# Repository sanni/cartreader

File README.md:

<br>    
<br>    
<br>   
<br>
We have moved, please visit us at https://github.com/oscartreader 🚀
<br>    
<br>    
<br>   
<br>
<br>    
<br>    
<br>   

# Open Source Cartridge Reader
This project represents a community-driven effort to provide an easy to build and easy to modify cartridge dumper.
Its main purpose is to dump a video game's ROM and save file to an SD card without the need of a PC.

For any questions you can use the [Discussions](https://github.com/sanni/cartreader/discussions) and/or [Issues](https://github.com/sanni/cartreader/issues) section here on GitHub, visit the accompanying thread in the [Arduino Forum](http://forum.arduino.cc/index.php?topic=158974.9001) or check out our [community discord server](https://discord.gg/YVxv7BnzXt), where you can reach most of the devs directly.

Also be sure to check the guides in the [Wiki](https://github.com/sanni/cartreader/wiki) too.

Happy making. 🔧🔨😊

#### Features:
- Modular design
- Stand-alone operation
- Easy to modify open-source code
- Portable when used together with a power bank

#### Supported Systems:
- NES/Famicom/Family Basic
- Super Nintendo/Super Famicom (including SF Memory, Satellaview, Sufami Turbo, and Game Processor RAM Cassettes)
- Nintendo 64 (including Controller Pak, Gameshark, and Xplorer 64)
- Game Boy Color (including GB Memory, Codebreaker, and Gameshark)
- Game Boy Advance
- Sega Mega Drive/Genesis
- Sega Master System

#### Supported with adapters:
- Virtual Boy
- Pokémon Mini
- Sega Game Gear
- Sega Mark III
- Sega SG-1000/SC-3000
- Sega Cards
- PC Engine/TurboGrafx-16/SuperGrafx
- WonderSwan (Color)
- NeoGeo Pocket (Color)
- Intellivision
- ColecoVision
- Benesse Pocket Challenge W
- Benesse Pocket Challenge V2
- Watara Supervision
- Atari 8-bit Computer (400/800/XL/XE)
- Atari 2600/5200/7800
- Atari Lynx
- Atari Jaguar
- Emerson Arcadia 2001
- Fairchild Channel F
- Magnavox Odyssey 2/Philips Videopac+
- Super A'Can
- MSX
- Casio PV-1000
- Casio Loopy
- Commodore VIC-20
- Commodore 64
- Vectrex
- Bally Astrocade
- Bandai Little Jammer
- Bandai Little Jammer Pro
- LeapFrog Leapster (L-MAX/Leapster2)
- RCA Studio II
- Texas Instruments TI-99
- Tomy Pyuuta
- TRS-80 Color Computer
- Vtech V.Smile (Baby/V.Motion)
- CPS3

#### Open Source Licenses:
- Software(everything in Cart_Reader folder) = GPL v3
- Hardware(everything in hardware folder) = CC BY 4.0
- Documentation(everything in the Wiki) = CC0 1.0

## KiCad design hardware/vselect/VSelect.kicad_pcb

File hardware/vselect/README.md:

# VSELECT: Automatic Voltage Selection Module

The VSELECT module automates voltage selection on HW5 by allowing the firmware to set the voltage. The module version is intended to be soldered in place of the voltage selection switch. You cannot use the VSELECT module and a power LED at the same time.

## Ordering the PCB and Installing the components

The VSELECT module requires SMD/SMC (surface-mounted devices/components) soldering. The pads have been extended slightly to aid in hand-soldering. While files suitable for use with JLCPCB's PCBA service have been included, these are unsuitable for most people to use due to the minimum order quantity. If you want fewer than 10 modules it will be cheaper to order them from someone selling pre-built ones.

## Installation

Instructions to build as well as to install the module have moved [to the wiki](https://github.com/sanni/cartreader/wiki/Automatic-Voltage-Selection).

## Configuration

The module requires code to function properly. The OSCR should still power on even without the code changes but the voltage will not automatically toggle. To enable automatic toggling, locate this bit of code:

```
/*==== HARDWARE MODULES ===========================================*/

/* [ Automatic Voltage Selection ---------------------------------- ]
    Enable this if you have the VSELECT module.
*/

//#define ENABLE_VSELECT
```

...and change it to:

```
/*==== HARDWARE MODULES ===========================================*/

/* [ Automatic Voltage Selection ---------------------------------- ]
    Enable this if you have the VSELECT module.
*/

#define ENABLE_VSELECT
```

After that simply update/program/flash your Arduino/OSCR as normal. Make sure you enable this every time you update. You can test that voltage switching is occurring with a multimeter by checking between ground and VCC.

## Updating
When the OSCR is using VSELECT-enabled firmware there are a few extra steps you need to take when flashing firmware. First, before connecting the OSCR to a computer, remove the SD card. Next, connect the OSCR to your computer and wait. Once it prompts you, press the button to set the voltage to 5V. Although you can flash the ATmega2560 while running at 3.3V it does not always work and seems more likely to cause the firmware to randomly be corrupt (sometimes right away, sometimes not for a few days). Although you can just reflash the firmware to it to resolve it, having to deal with it is rather inconvenient.

## Troubleshooting
If the 3.3V rail is not powered (i.e. you forgot to solder the jumper on the LCD) then when the module tries to switch to that it will power off the VCC rail. This will appear as a reboot loop where you'll see it briefly power on and then immediately power off only to immediately power on again. This is because the module starts in 5V mode and switches to 3.3V after the system boots and tells it to do so.

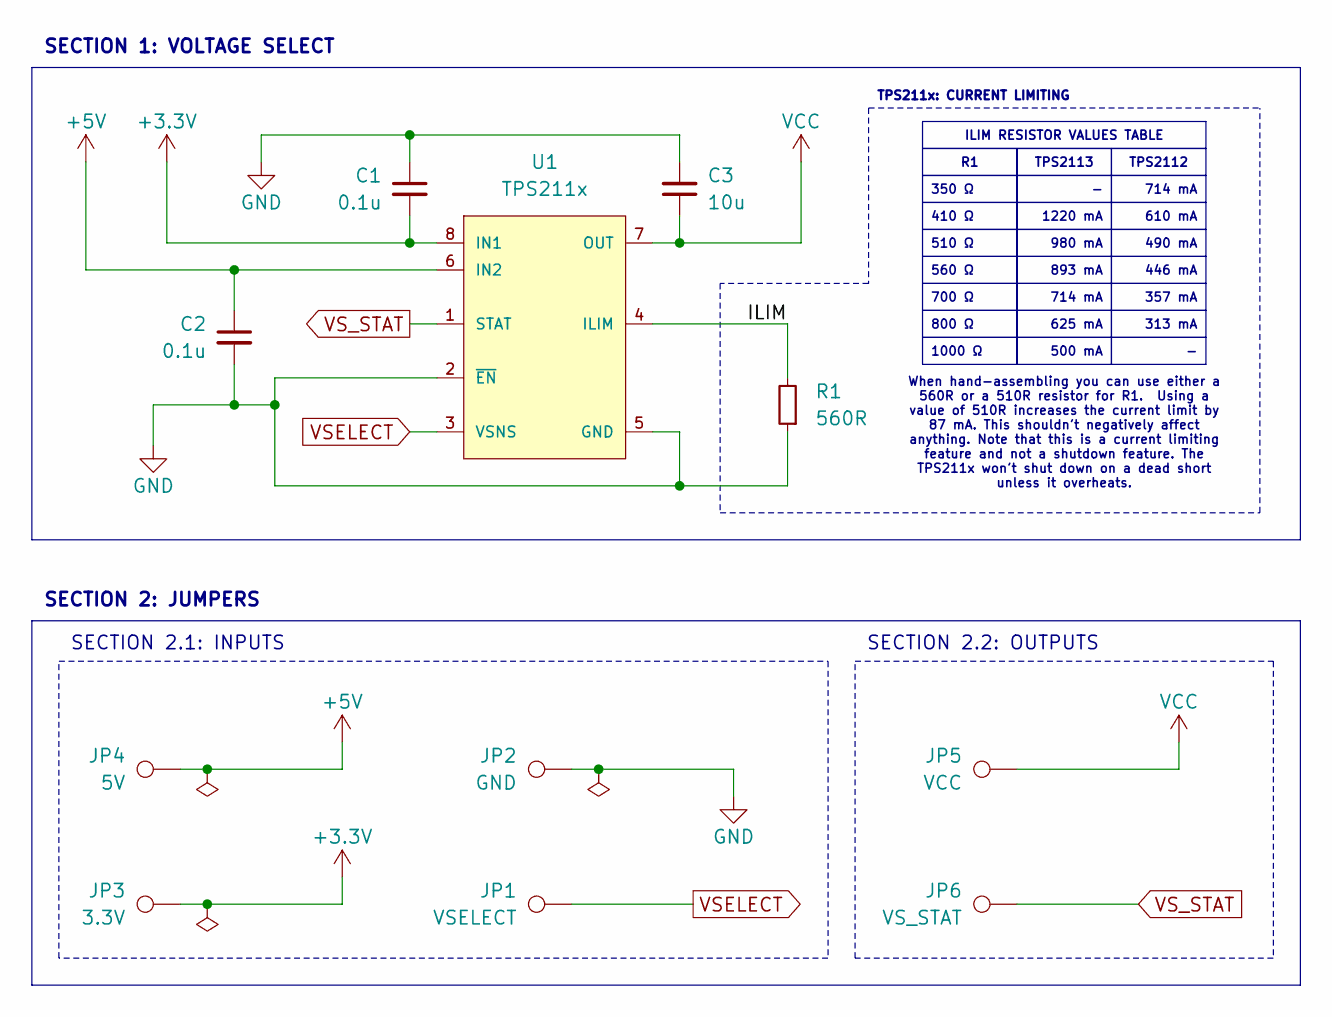
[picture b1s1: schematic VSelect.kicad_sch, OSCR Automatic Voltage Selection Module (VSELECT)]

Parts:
C1, C2: 0.1u; C_0402_1005Metric_Pad0.74x0.62mm_HandSolder; Part CL05B104KO5NNNC; LCSC C1525
C3: 10u; C_0402_1005Metric_Pad0.74x0.62mm_HandSolder; Part CL05A106MQ5NUNC; LCSC C15525
JP1: VSELECT; TestPoint_Pad_2.0x2.0mm
JP2: GND; TestPoint_Pad_2.0x2.0mm
JP3: 3.3V; Header - VSELECT - Switch Pad
JP4: 5V; Header - VSELECT - Switch Pad
JP5: VCC; Header - VSELECT - Switch Pad
JP6: VS_STAT; TestPoint_Pad_2.0x2.0mm
R1: 560R; R_0402_1005Metric_Pad0.72x0.64mm_HandSolder; Part 0402WGF5100TCE; LCSC C25123
U1: TPS211x; IC - VSELECT - TPS2113; Part Hand/TPS2113APWR (C130052); Machine/TPS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; LCSC C354512

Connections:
+3.3V: C1.2, JP3.1, U1.8 (IN1)
+5V: C2.1, JP4.1, U1.6 (IN2)
/ILIM: R1.2, U1.4 (ILIM)
GND: C1.1, C2.2, C3.2, JP2.1, R1.1, U1.2 (~EN), U1.5 (GND), U1.9 (GND)
VCC: C3.1, JP5.1, U1.7 (OUT)
VSELECT: JP1.1, U1.3 (VSNS)
VS_STAT: JP6.1, U1.1 (STAT)

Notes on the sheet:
350 Ω
SECTION 2: JUMPERS
700 Ω
TPS2113
510 Ω
446 mA
490 mA
980 mA
893 mA
1000 Ω
714 mA
313 mA
TPS211x: CURRENT LIMITING
500 mA
625 mA
560 Ω
357 mA
SECTION 2.2: OUTPUTS
610 mA
1220 mA
410 Ω
SECTION 2.1: INPUTS
ILIM RESISTOR VALUES TABLE
TPS2112
800 Ω
SECTION 1: VOLTAGE SELECT
When hand-assembling you can use either a 560R or a 510R resistor for R1. Using a value of 510R increases the current limit by 87 mA. This shouldn't negatively affect anything. Note that this is a current limiting feature and not a shutdown feature. The TPS211x won't shut down on a dead short unles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

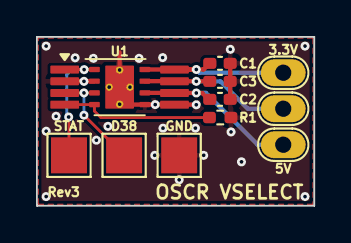
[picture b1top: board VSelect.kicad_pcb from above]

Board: 2 copper layers, 15.4 x 9.4 mm, 11 parts (0 on the bottom side), 7 nets.

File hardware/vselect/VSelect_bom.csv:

Designator,Footprint,Quantity,Value,LCSC Part #
"C1, C2",0402,2,0.1u,C1525
C3,0402,1,10u,C15525
R1,0402,1,560R,C25123
U1,IC - VSELECT - TPS2113,1,TPS211x,C354512

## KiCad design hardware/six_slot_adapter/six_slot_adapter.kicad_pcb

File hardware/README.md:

## All the files in this directory are licensed under the Attribution 4.0 International (CC BY 4.0)     

### This means that you are free to:    
- Share - copy and redistribute the material in any medium or format    
- Adapt - remix, transform, and build upon the material for any purpose, even commercially.  

The licensor cannot revoke these freedoms as long as you follow the license terms.    

### Under the following terms:    
- Attribution - You must give appropriate credit, provide a link to the license, and indicate if changes were made. You may do so in any reasonable manner, but not in any way that suggests the licensor endorses you or your use.    
- No additional restrictions - You may not apply legal terms or technological measures that legally restrict others from doing anything the license permits.    

More details: https://creativecommons.org/licenses/by/4.0/

##

You can view the schematic and PCB files using [KiCad](https://www.kicad.org/).   
To design your own adapters you can follow this [tutorial](https://github.com/sanni/cartreader/wiki/Designing-your-own-Adapters)   
Also check out the user contributions for even more adapters: https://github.com/sanni/cartreader/discussions/354

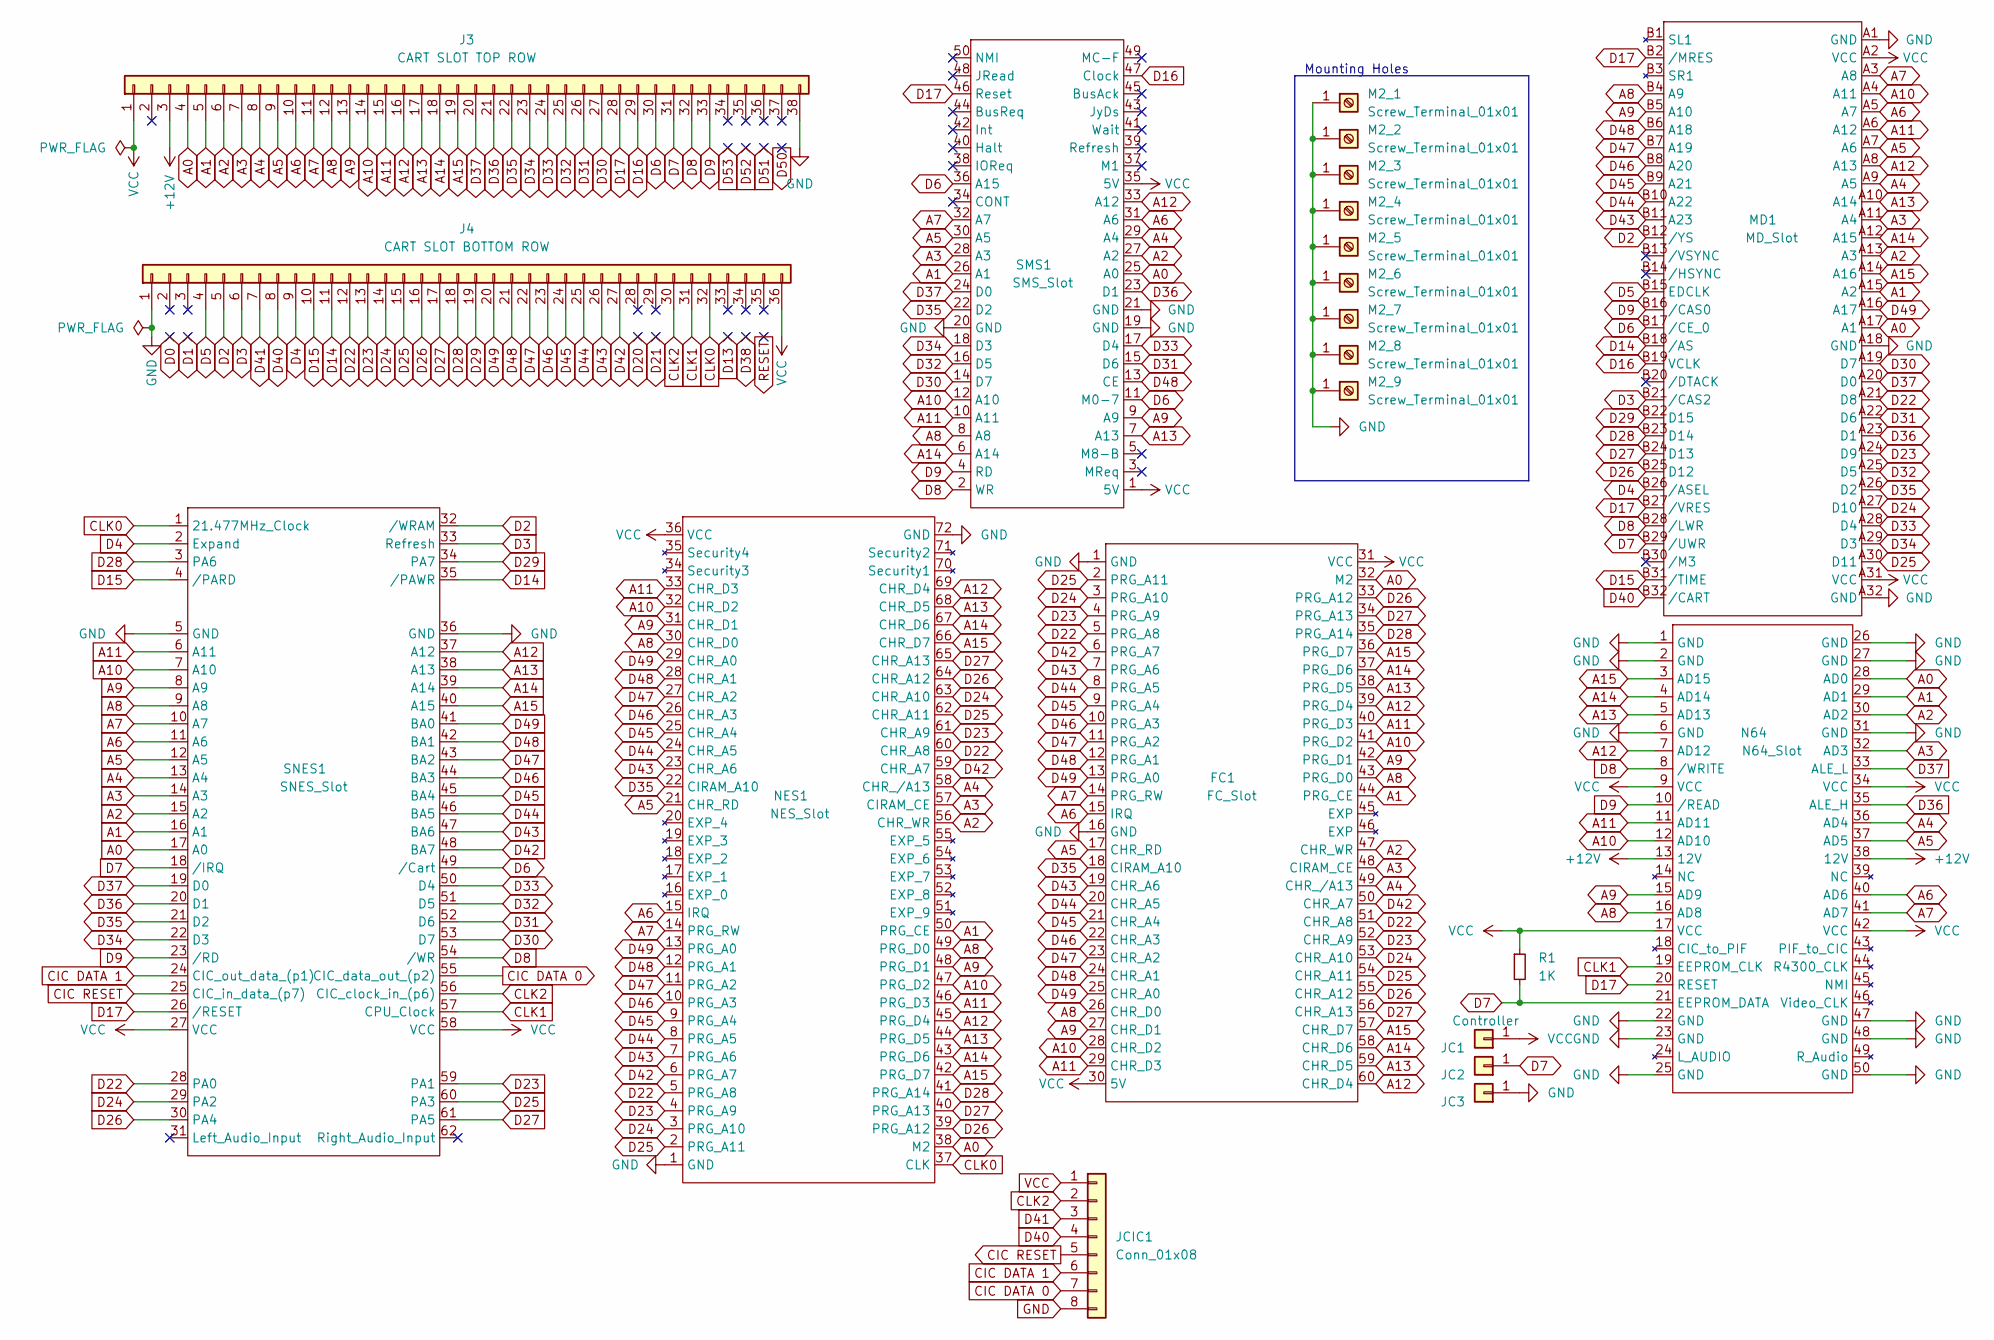
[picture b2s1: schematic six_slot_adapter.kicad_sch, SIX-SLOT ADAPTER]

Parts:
FC1: FC_Slot
J3: CART SLOT TOP ROW; PinSocket_1x38_P2.54mm_Vertical
J4: CART SLOT BOTTOM ROW; PinSocket_1x36_P2.54mm_Vertical
JC1: Controller; PinHeader_1x01_P2.54mm_Vertical
JC2, JC3: Conn_01x01; PinHeader_1x01_P2.54mm_Vertical
JCIC1: Conn_01x08; PinHeader_1x08_P2.54mm_Vertical
M2_1, M2_2, M2_3, M2_4, M2_5, M2_6, M2_7, M2_8, M2_9: Screw_Terminal_01x01; MountingHole_2.2mm_M2_ISO7380_Pad
MD1: MD_Slot
N64: N64_Slot; N64 Slot
NES1: NES_Slot
R1: 1K; R_Axial_DIN0207_L6.3mm_D2.5mm_P10.16mm_Horizontal
SMS1: SMS_Slot
SNES1: SNES_Slot; SNES Slot

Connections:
+12V: J3.3, N64.13 (12V), N64.38 (12V)
A0: FC1.32 (M2), J3.4, MD1.A17 (A1), N64.28 (AD0), NES1.38 (M2), SMS1.25 (A0), SNES1.17 (A0)
A1: FC1.44 (PRG_CE), J3.5, MD1.A15 (A2), N64.29 (AD1), NES1.50 (PRG_CE), SMS1.26 (A1), SNES1.16 (A1)
A2: FC1.47 (CHR_WR), J3.6, MD1.A13 (A3), N64.30 (AD2), NES1.56 (CHR_WR), SMS1.27 (A2), SNES1.15 (A2)
A3: FC1.48 (CIRAM_CE), J3.7, MD1.A11 (A4), N64.32 (AD3), NES1.57 (CIRAM_CE), SMS1.28 (A3), SNES1.14 (A3)
A4: FC1.49 (CHR_/A13), J3.8, MD1.A9 (A5), N64.36 (AD4), NES1.58 (CHR_/A13), SMS1.29 (A4), SNES1.13 (A4)
A5: FC1.17 (CHR_RD), J3.9, MD1.A7 (A6), N64.37 (AD5), NES1.21 (CHR_RD), SMS1.30 (A5), SNES1.12 (A5)
A6: FC1.15 (IRQ), J3.10, MD1.A5 (A7), N64.40 (AD6), NES1.15 (IRQ), SMS1.31 (A6), SNES1.11 (A6)
A7: FC1.14 (PRG_RW), J3.11, MD1.A3 (A8), N64.41 (AD7), NES1.14 (PRG_RW), SMS1.32 (A7), SNES1.10 (A7)
A8: FC1.26 (CHR_D0), FC1.43 (PRG_D0), J3.12, MD1.B4 (A9), N64.16 (AD8), NES1.30 (CHR_D0), NES1.49 (PRG_D0), SMS1.8 (A8), SNES1.9 (A8)
A9: FC1.27 (CHR_D1), FC1.42 (PRG_D1), J3.13, MD1.B5 (A10), N64.15 (AD9), NES1.31 (CHR_D1), NES1.48 (PRG_D1), SMS1.9 (A9), SNES1.8 (A9)
A10: FC1.28 (CHR_D2), FC1.41 (PRG_D2), J3.14, MD1.A4 (A11), N64.12 (AD10), NES1.32 (CHR_D2), NES1.47 (PRG_D2), SMS1.12 (A10), SNES1.7 (A10)
A11: FC1.29 (CHR_D3), FC1.40 (PRG_D3), J3.15, MD1.A6 (A12), N64.11 (AD11), NES1.33 (CHR_D3), NES1.46 (PRG_D3), SMS1.10 (A11), SNES1.6 (A11)
A12: FC1.39 (PRG_D4), FC1.60 (CHR_D4), J3.16, MD1.A8 (A13), N64.7 (AD12), NES1.45 (PRG_D4), NES1.69 (CHR_D4), SMS1.33 (A12), SNES1.37 (A12)
A13: FC1.38 (PRG_D5), FC1.59 (CHR_D5), J3.17, MD1.A10 (A14), N64.5 (AD13), NES1.44 (PRG_D5), NES1.68 (CHR_D5), SMS1.7 (A13), SNES1.38 (A13)
A14: FC1.37 (PRG_D6), FC1.58 (CHR_D6), J3.18, MD1.A12 (A15), N64.4 (AD14), NES1.43 (PRG_D6), NES1.67 (CHR_D6), SMS1.6 (A14), SNES1.39 (A14)
A15: FC1.36 (PRG_D7), FC1.57 (CHR_D7), J3.19, MD1.A14 (A16), N64.3 (AD15), NES1.42 (PRG_D7), NES1.66 (CHR_D7), SNES1.40 (A15)
CIC DATA 0: JCIC1.7, SNES1.55 (CIC_data_out_(p2))
CIC DATA 1: JCIC1.6, SNES1.24 (CIC_out_data_(p1))
CIC RESET: JCIC1.5, SNES1.25 (CIC_in_data_(p7))
CLK0: J4.32, NES1.37 (CLK), SNES1.1 (21.477MHz_Clock)
CLK1: J4.31, N64.19 (EEPROM_CLK), SNES1.57 (CPU_Clock)
CLK2: J4.30, JCIC1.2, SNES1.56 (CIC_clock_in_(p6))
D2: J4.5, MD1.B12 (/YS), SNES1.32 (/WRAM)
D3: J4.6, MD1.B21 (/CAS2), SNES1.33 (Refresh)
D4: J4.9, MD1.B26 (/ASEL), SNES1.2 (Expand)
D5: J4.4, MD1.B15 (EDCLK)
D6: J3.30, MD1.B17 (/CE_0), SMS1.11 (M0-7), SMS1.36 (A15), SNES1.49 (/Cart)
D7: J3.31, JC2.1, MD1.B29 (/UWR), N64.21 (EEPROM_DATA), R1.2, SNES1.18 (/IRQ)
D8: J3.32, MD1.B28 (/LWR), N64.8 (/WRITE), SMS1.2 (WR), SNES1.54 (/WR)
D9: J3.33, MD1.B16 (/CAS0), N64.10 (/READ), SMS1.4 (RD), SNES1.23 (/RD)
D14: J4.11, MD1.B18 (/AS), SNES1.35 (/PAWR)
D15: J4.10, MD1.B31 (/TIME), SNES1.4 (/PARD)
D16: J3.29, MD1.B19 (VCLK), SMS1.47 (Clock)
D17: J3.28, MD1.B2 (/MRES), MD1.B27 (/VRES), N64.20 (RESET), SMS1.46 (Reset), SNES1.26 (/RESET)
D22: FC1.5 (PRG_A8), FC1.51 (CHR_A8), J4.12, MD1.A21 (D8), NES1.5 (PRG_A8), NES1.60 (CHR_A8), SNES1.28 (PA0)
D23: FC1.4 (PRG_A9), FC1.52 (CHR_A9), J4.13, MD1.A24 (D9), NES1.4 (PRG_A9), NES1.61 (CHR_A9), SNES1.59 (PA1)
D24: FC1.3 (PRG_A10), FC1.53 (CHR_A10), J4.14, MD1.A27 (D10), NES1.3 (PRG_A10), NES1.63 (CHR_A10), SNES1.29 (PA2)
D25: FC1.2 (PRG_A11), FC1.54 (CHR_A11), J4.15, MD1.A30 (D11), NES1.2 (PRG_A11), NES1.62 (CHR_A11), SNES1.60 (PA3)
D26: FC1.33 (PRG_A12), FC1.55 (CHR_A12), J4.16, MD1.B25 (D12), NES1.39 (PRG_A12), NES1.64 (CHR_A12), SNES1.30 (PA4)
D27: FC1.34 (PRG_A13), FC1.56 (CHR_A13), J4.17, MD1.B24 (D13), NES1.40 (PRG_A13), NES1.65 (CHR_A13), SNES1.61 (PA5)
D28: FC1.35 (PRG_A14), J4.18, MD1.B23 (D14), NES1.41 (PRG_A14), SNES1.3 (PA6)
D29: J4.19, MD1.B22 (D15), SNES1.34 (PA7)
D30: J3.27, MD1.A19 (D7), SMS1.14 (D7), SNES1.53 (D7)
D31: J3.26, MD1.A22 (D6), SMS1.15 (D6), SNES1.52 (D6)
D32: J3.25, MD1.A25 (D5), SMS1.16 (D5), SNES1.51 (D5)
D33: J3.24, MD1.A28 (D4), SMS1.17 (D4), SNES1.50 (D4)
D34: J3.23, MD1.A29 (D3), SMS1.18 (D3), SNES1.22 (D3)
D35: FC1.18 (CIRAM_A10), J3.22, MD1.A26 (D2), NES1.22 (CIRAM_A10), SMS1.22 (D2), SNES1.21 (D2)
D36: J3.21, MD1.A23 (D1), N64.35 (ALE_H), SMS1.23 (D1), SNES1.20 (D1)
D37: J3.20, MD1.A20 (D0), N64.33 (ALE_L), SMS1.24 (D0), SNES1.19 (D0)
D40: J4.8, JCIC1.4, MD1.B32 (/CART)
D41: J4.7, JCIC1.3
D42: FC1.6 (PRG_A7), FC1.50 (CHR_A7), J4.27, NES1.6 (PRG_A7), NES1.59 (CHR_A7), SNES1.48 (BA7)
D43: FC1.7 (PRG_A6), FC1.19 (CHR_A6), J4.26, MD1.B11 (A23), NES1.7 (PRG_A6), NES1.23 (CHR_A6), SNES1.47 (BA6)
D44: FC1.8 (PRG_A5), FC1.20 (CHR_A5), J4.25, MD1.B10 (A22), NES1.8 (PRG_A5), NES1.24 (CHR_A5), SNES1.46 (BA5)
D45: FC1.9 (PRG_A4), FC1.21 (CHR_A4), J4.24, MD1.B9 (A21), NES1.9 (PRG_A4), NES1.25 (CHR_A4), SNES1.45 (BA4)
D46: FC1.10 (PRG_A3), FC1.22 (CHR_A3), J4.23, MD1.B8 (A20), NES1.10 (PRG_A3), NES1.26 (CHR_A3), SNES1.44 (BA3)
D47: FC1.11 (PRG_A2), FC1.23 (CHR_A2), J4.22, MD1.B7 (A19), NES1.11 (PRG_A2), NES1.27 (CHR_A2), SNES1.43 (BA2)
D48: FC1.12 (PRG_A1), FC1.24 (CHR_A1), J4.21, MD1.B6 (A18), NES1.12 (PRG_A1), NES1.28 (CHR_A1), SMS1.13 (CE), SNES1.42 (BA1)
D49: FC1.13 (PRG_A0), FC1.25 (CHR_A0), J4.20, MD1.A16 (A17), NES1.13 (PRG_A0), NES1.29 (CHR_A0), SNES1.41 (BA0)
GND: FC1.1 (GND), FC1.16 (GND), J3.38, J4.1, JC3.1, JCIC1.8, M2_1.1, M2_2.1, M2_3.1, M2_4.1, M2_5.1, M2_6.1, M2_7.1, M2_8.1, M2_9.1, MD1.A1 (GND), MD1.A18 (GND), MD1.A32 (GND), N64.1 (GND), N64.2 (GND), N64.6 (GND), N64.22 (GND), N64.23 (GND), N64.25 (GND), N64.26 (GND), N64.27 (GND), N64.31 (GND), N64.47 (GND), N64.48 (GND), N64.50 (GND), NES1.1 (GND), NES1.72 (GND), SMS1.19 (GND), SMS1.20 (GND), SMS1.21 (GND), SNES1.5 (GND), SNES1.36 (GND)
VCC: FC1.30 (5V), FC1.31 (VCC), J3.1, J4.36, JC1.1, JCIC1.1, MD1.A2 (VCC), MD1.A31 (VCC), N64.9 (VCC), N64.17 (VCC), N64.34 (VCC), N64.42 (VCC), NES1.36 (VCC), R1.1, SMS1.1 (5V), SMS1.35 (5V), SNES1.27 (VCC), SNES1.58 (VCC)

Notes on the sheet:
Mounting Holes

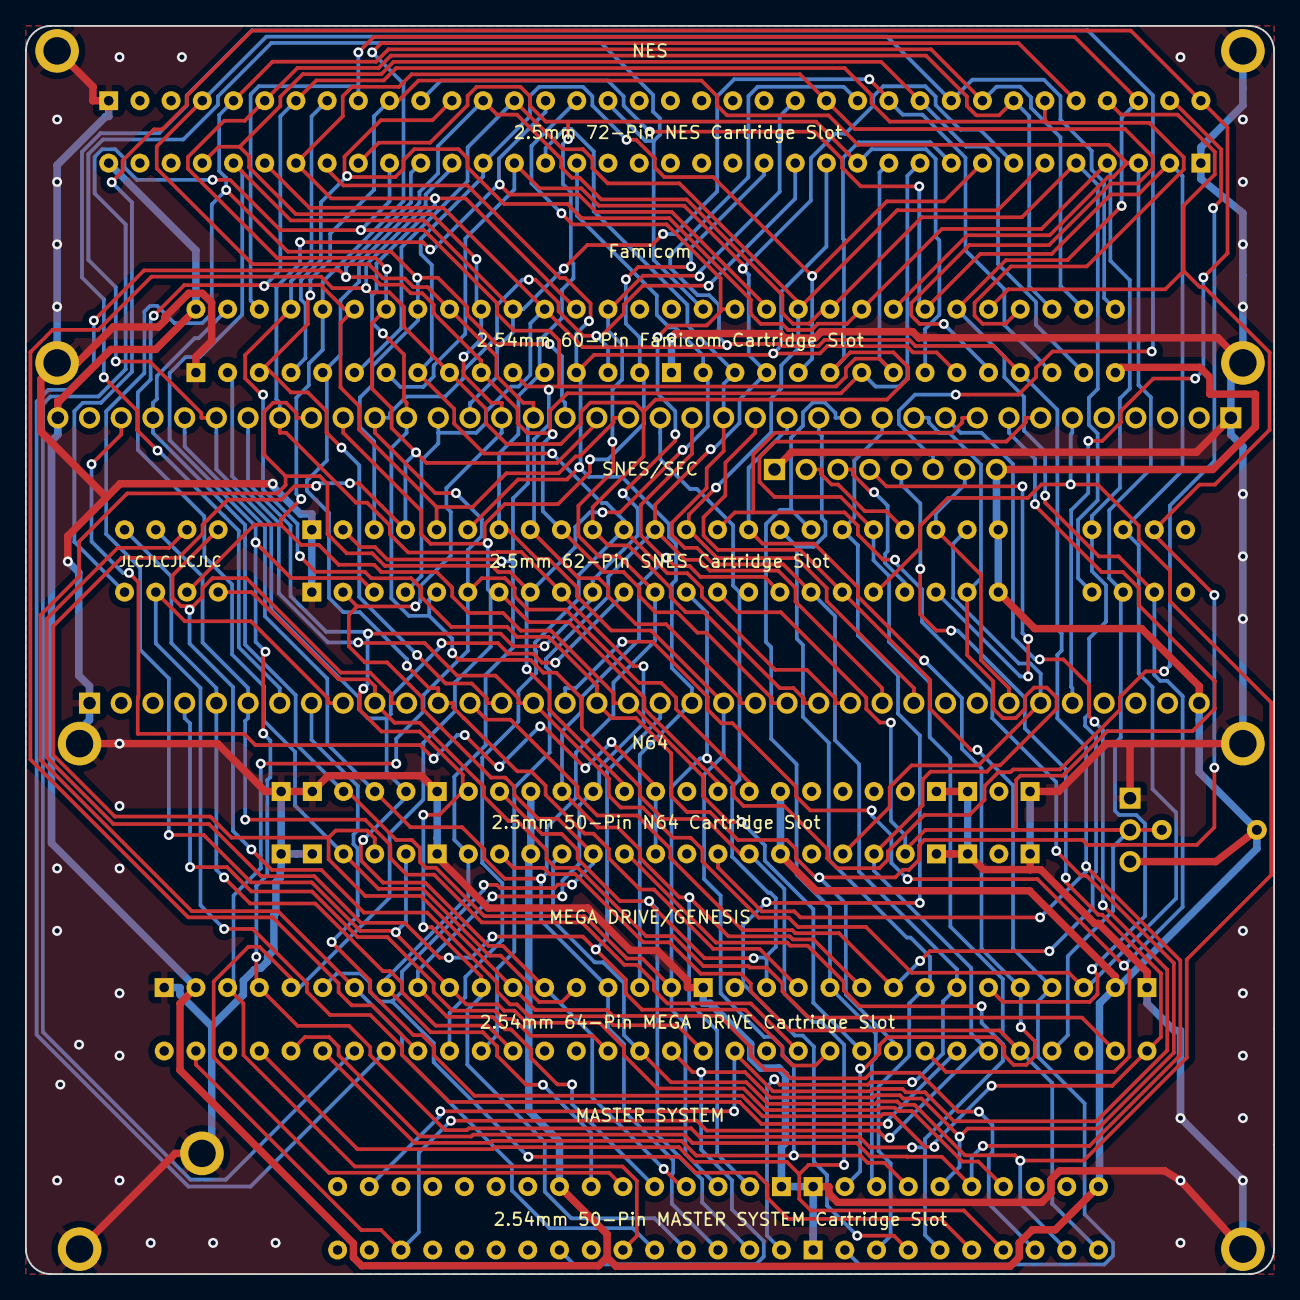
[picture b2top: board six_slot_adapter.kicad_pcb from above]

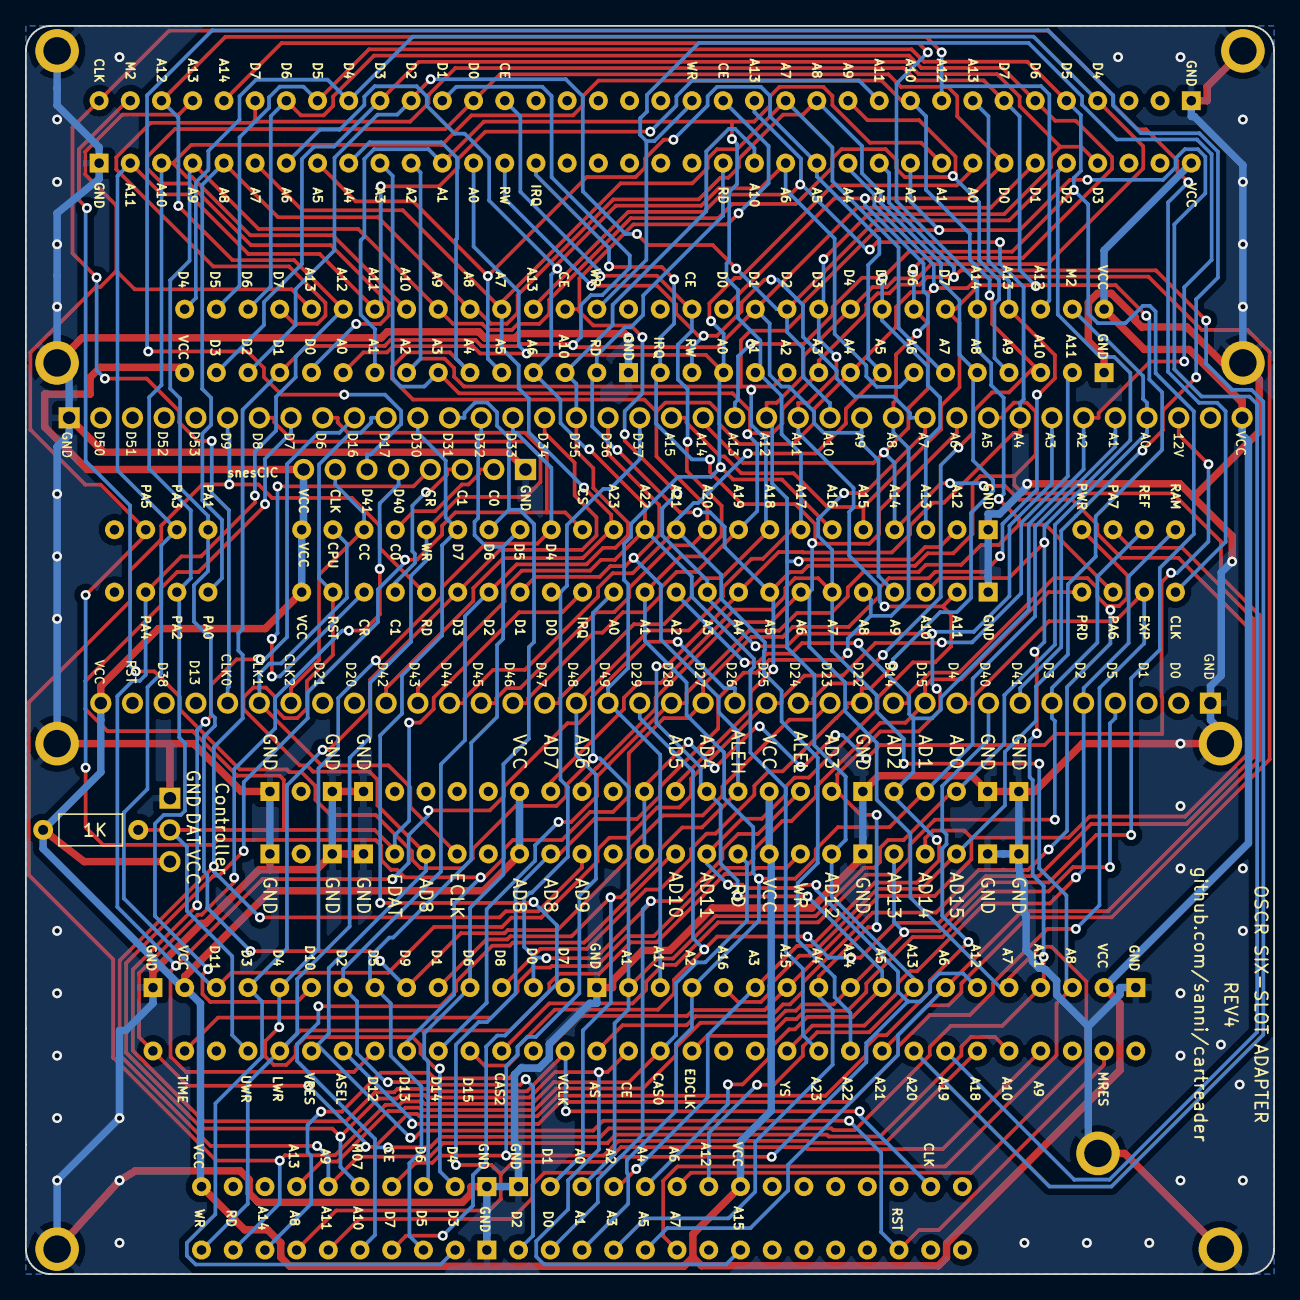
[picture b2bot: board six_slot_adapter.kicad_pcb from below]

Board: 2 copper layers, 100.0 x 100.0 mm, 22 parts (11 on the bottom side), 63 nets.

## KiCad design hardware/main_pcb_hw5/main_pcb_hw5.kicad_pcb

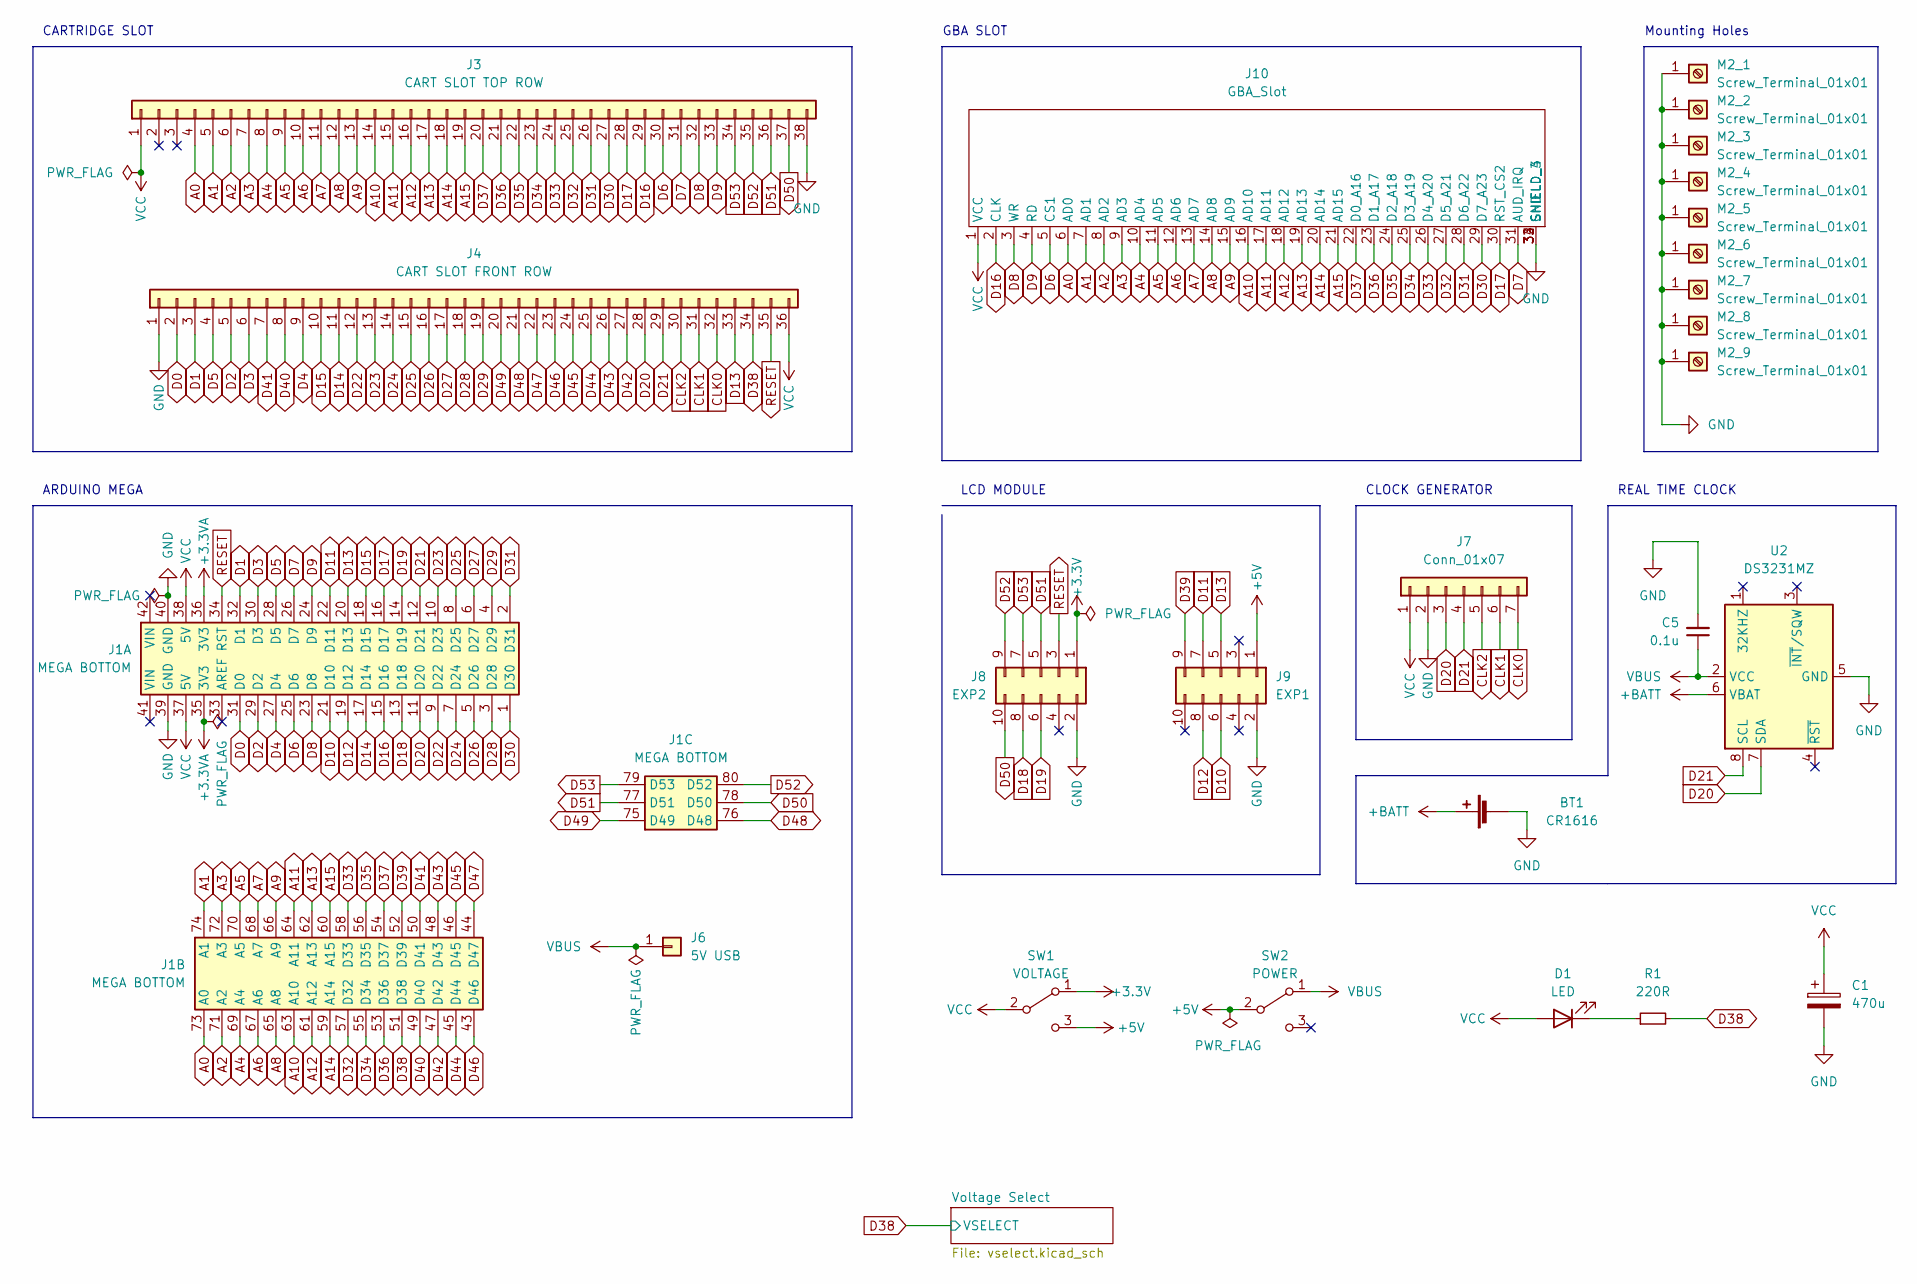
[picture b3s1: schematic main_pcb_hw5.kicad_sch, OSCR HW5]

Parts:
BT1: CR1616
C1: 470u; CP_Radial_D8.0mm_P3.50mm
C5: 0.1u; C_0402_1005Metric_Pad0.74x0.62mm_HandSolder; JLCPCB C307331
D1: LED; LED_D3.0mm
J1: MEGA BOTTOM; MEGA2560_PRO_MINI
J3: CART SLOT TOP ROW; Cartridge_Port_Adapter-Back
J4: CART SLOT FRONT ROW; Cartridge_Port_Adapter-Front
J6: 5V USB; PinHeader_1x01_P2.54mm_Vertical
J7: Conn_01x07; Clock_Generator_Header
J8: EXP2; LCD_Header
J9: EXP1; LCD_Header
J10: GBA_Slot
M2_1, M2_2, M2_3, M2_4, M2_5, M2_6, M2_7, M2_8, M2_9: Screw_Terminal_01x01
R1: 220R; R_Axial_DIN0207_L6.3mm_D2.5mm_P10.16mm_Horizontal
SW1: VOLTAGE; Power_Switch
SW2: POWER; Power_Switch
U2: DS3231MZ; SOIC-8_3.9x4.9mm_P1.27mm

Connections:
+3.3VA: J1.35 (3V3), J1.36 (3V3)
+5V: J9.1, SW1.3 (C), SW2.2 (B); also elsewhere on the board
+BATT: BT1.1 (+), U2.6 (VBAT)
A0: J1.73 (A0), J3.4, J10.6 (AD0)
A1: J1.74 (A1), J3.5, J10.7 (AD1)
A2: J1.71 (A2), J3.6, J10.8 (AD2)
A3: J1.72 (A3), J3.7, J10.9 (AD3)
A4: J1.69 (A4), J3.8, J10.10 (AD4)
A5: J1.70 (A5), J3.9, J10.11 (AD5)
A6: J1.67 (A6), J3.10, J10.12 (AD6)
A7: J1.68 (A7), J3.11, J10.13 (AD7)
A8: J1.65 (A8), J3.12, J10.14 (AD8)
A9: J1.66 (A9), J3.13, J10.15 (AD9)
A10: J1.63 (A10), J3.14, J10.16 (AD10)
A11: J1.64 (A11), J3.15, J10.17 (AD11)
A12: J1.61 (A12), J3.16, J10.18 (AD12)
A13: J1.62 (A13), J3.17, J10.19 (AD13)
A14: J1.59 (A14), J3.18, J10.20 (AD14)
A15: J1.60 (A15), J3.19, J10.21 (AD15)
CLK0: J4.32, J7.7
CLK1: J4.31, J7.6
CLK2: J4.30, J7.5
D0: J1.31 (D0), J4.2
D1: J1.32 (D1), J4.3
D2: J1.29 (D2), J4.5
D3: J1.30 (D3), J4.6
D4: J1.27 (D4), J4.9
D5: J1.28 (D5), J4.4
D6: J1.25 (D6), J3.30, J10.5 (CS1)
D7: J1.26 (D7), J3.31, J10.31 (AUD_IRQ)
D8: J1.23 (D8), J3.32, J10.3 (WR)
D9: J1.24 (D9), J3.33, J10.4 (RD)
D10: J1.21 (D10), J9.6
D11: J1.22 (D11), J9.7
D12: J1.19 (D12), J9.8
D13: J1.20 (D13), J4.33, J9.5
D14: J1.17 (D14), J4.11
D15: J1.18 (D15), J4.10
D16: J1.15 (D16), J3.29, J10.2 (CLK)
D17: J1.16 (D17), J3.28, J10.30 (RST_CS2)
D18: J1.13 (D18), J8.8
D19: J1.14 (D19), J8.6
D20: J1.11 (D20), J4.28, J7.3, U2.7 (SDA)
D21: J1.12 (D21), J4.29, J7.4, U2.8 (SCL)
D22: J1.9 (D22), J4.12
D23: J1.10 (D23), J4.13
D24: J1.7 (D24), J4.14
D25: J1.8 (D25), J4.15
D26: J1.5 (D26), J4.16
D27: J1.6 (D27), J4.17
D28: J1.3 (D28), J4.18
D29: J1.4 (D29), J4.19
D30: J1.1 (D30), J3.27, J10.29 (D7_A23)
D31: J1.2 (D31), J3.26, J10.28 (D6_A22)
D32: J1.57 (D32), J3.25, J10.27 (D5_A21)
D33: J1.58 (D33), J3.24, J10.26 (D4_A20)
D34: J1.55 (D34), J3.23, J10.25 (D3_A19)
D35: J1.56 (D35), J3.22, J10.24 (D2_A18)
D36: J1.53 (D36), J3.21, J10.23 (D1_A17)
D37: J1.54 (D37), J3.20, J10.22 (D0_A16)
D38: J1.51 (D38), J4.34, R1.2; also elsewhere on the board
D39: J1.52 (D39), J9.9
D40: J1.49 (D40), J4.8
D41: J1.50 (D41), J4.7
D42: J1.47 (D42), J4.27
D43: J1.48 (D43), J4.26
D44: J1.45 (D44), J4.25
D45: J1.46 (D45), J4.24
D46: J1.43 (D46), J4.23
D47: J1.44 (D47), J4.22
D48: J1.76 (D48), J4.21
D49: J1.75 (D49), J4.20
D50: J1.78 (D50), J3.37, J8.10
D51: J1.77 (D51), J3.36, J8.5
D52: J1.80 (D52), J3.35, J8.9
D53: J1.79 (D53), J3.34, J8.7
GND: BT1.2 (-), C1.2, C5.2, J1.39 (GND), J1.40 (GND), J3.38, J4.1, J7.2, J8.2, J9.2, J10.32 (GND), J10.33 (SHIELD_3), J10.34 (SHIELD_4), M2_1.1, M2_2.1, M2_3.1, M2_4.1, M2_5.1, M2_6.1, M2_7.1, M2_8.1, M2_9.1, U2.5 (GND); also elsewhere on the board
unnamed: D1.1 (K), R1.1
RESET: J1.34 (RST), J4.35, J8.3
VBUS: C5.1, J6.1, SW2.1 (A), U2.2 (VCC)
VCC: C1.1, D1.2 (A), J1.37 (5V), J1.38 (5V), J3.1, J4.36, J7.1, J10.1 (VCC), SW1.2 (B); also elsewhere on the board

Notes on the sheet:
LCD MODULE
REAL TIME CLOCK
CLOCK GENERATOR
CARTRIDGE SLOT
GBA SLOT
ARDUINO MEGA
Mounting Holes

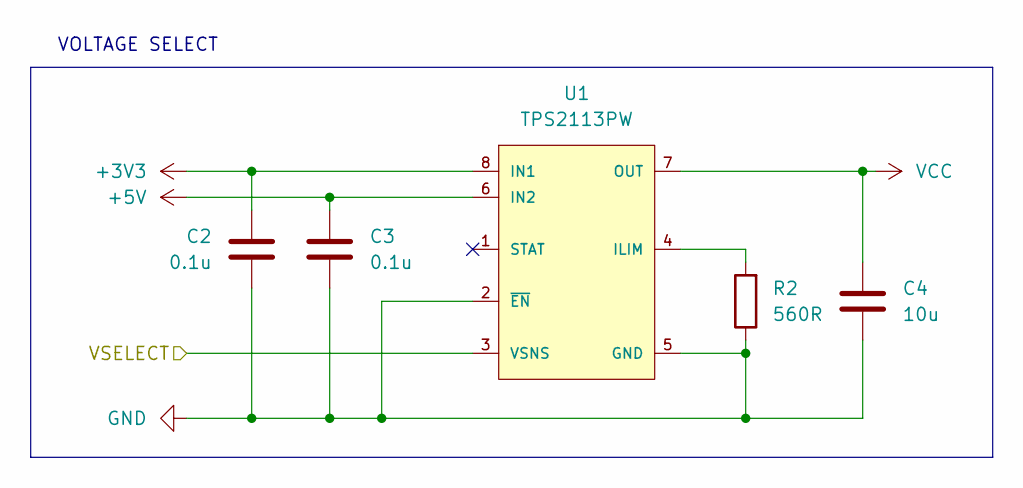
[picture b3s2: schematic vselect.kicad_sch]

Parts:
C2, C3: 0.1u; C_0402_1005Metric_Pad0.74x0.62mm_HandSolder; JLCPCB C307331
C4: 10u; C_0402_1005Metric_Pad0.74x0.62mm_HandSolder; JLCPCB C15525
R2: 560R; R_0402_1005Metric_Pad0.72x0.64mm_HandSolder; JLCPCB C137858
U1: TPS2113PW; Texas_Instruments-TPS2113PW-Level_A

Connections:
+5V: C3.1, U1.6 (IN2); also elsewhere on the board
D38: U1.3 (VSNS); also elsewhere on the board
GND: C2.1, C3.2, C4.2, R2.1, U1.2 (~EN), U1.5 (GND); also elsewhere on the board
unnamed: R2.2, U1.4 (ILIM)
VCC: C4.1, U1.7 (OUT); also elsewhere on the board

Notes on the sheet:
VOLTAGE SELECT

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
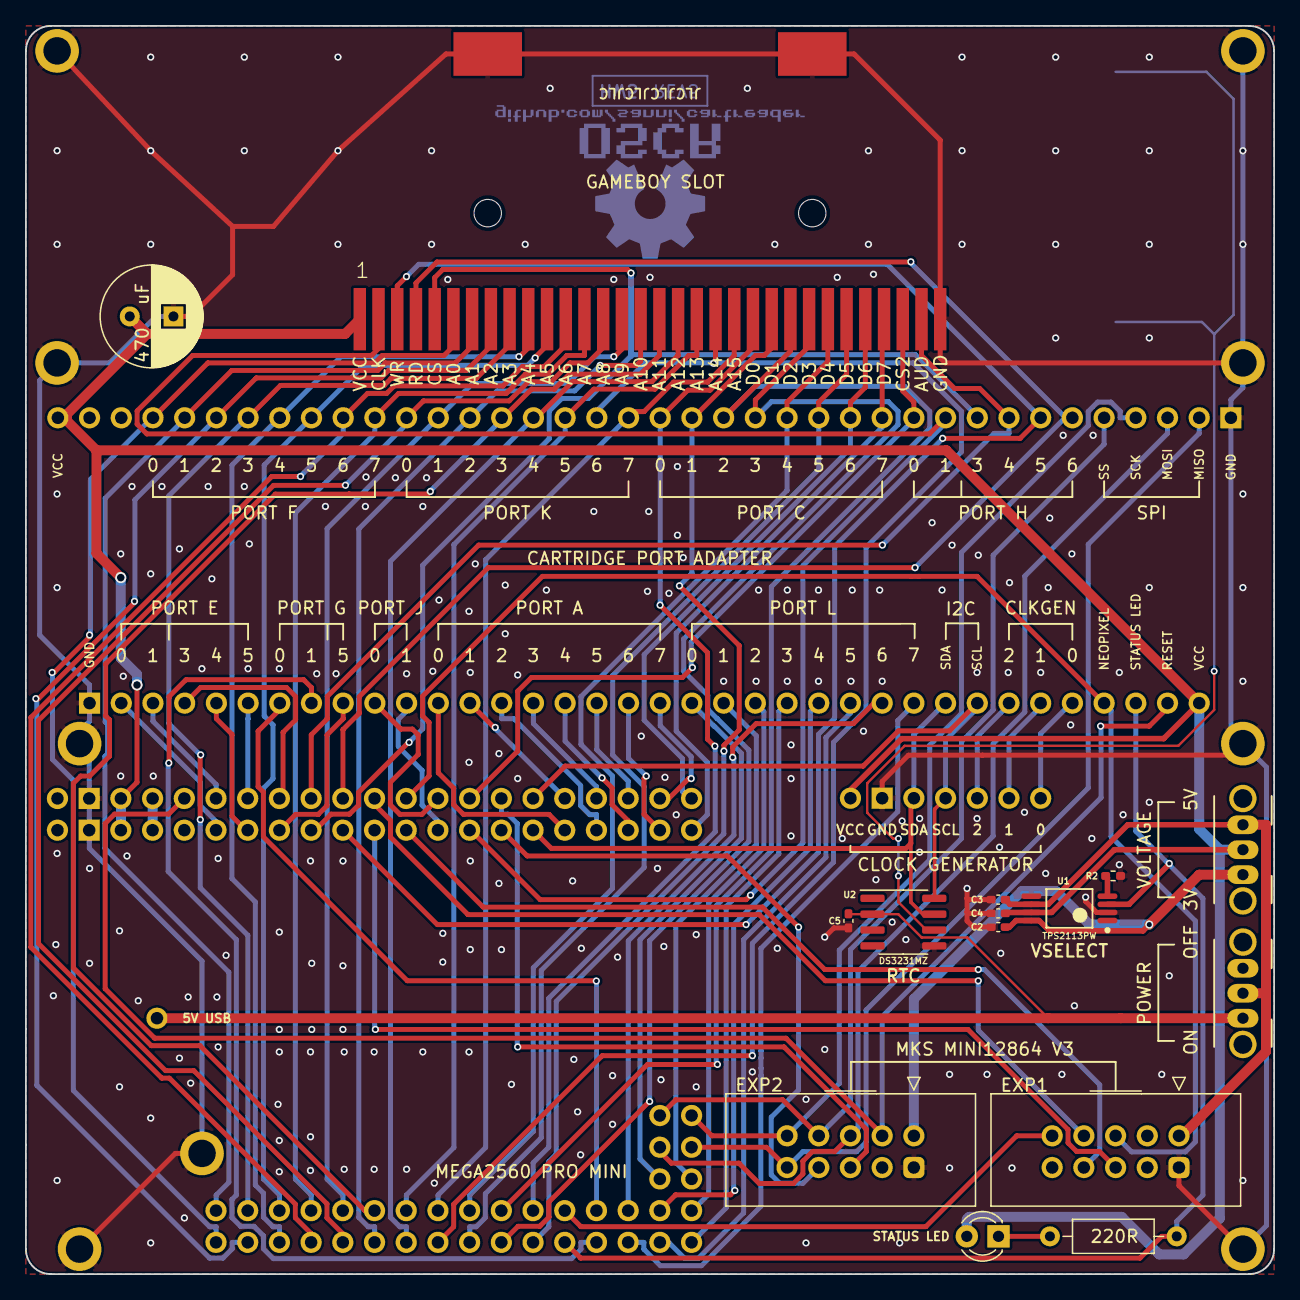
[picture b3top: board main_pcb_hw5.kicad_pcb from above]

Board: 2 copper layers, 100.0 x 100.0 mm, 30 parts (1 on the bottom side), 83 nets.
